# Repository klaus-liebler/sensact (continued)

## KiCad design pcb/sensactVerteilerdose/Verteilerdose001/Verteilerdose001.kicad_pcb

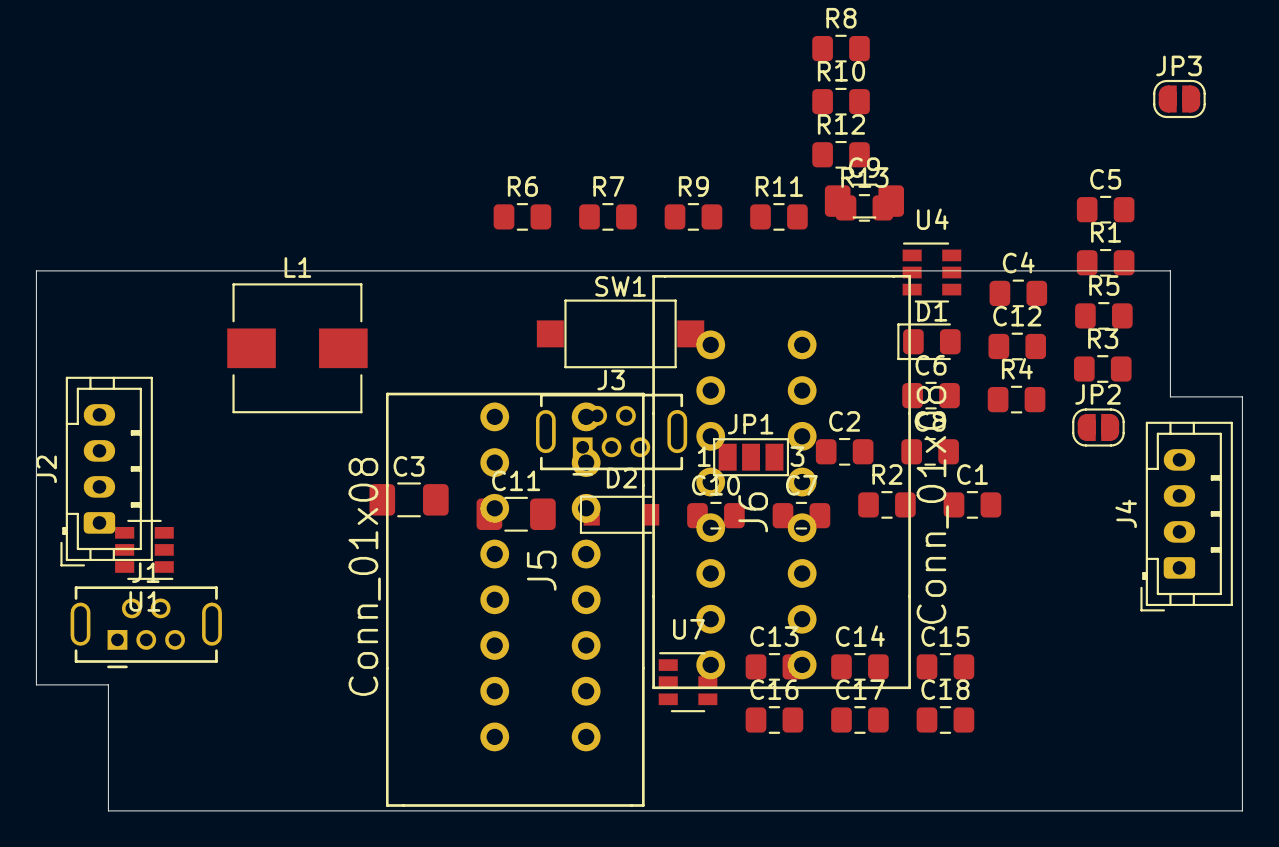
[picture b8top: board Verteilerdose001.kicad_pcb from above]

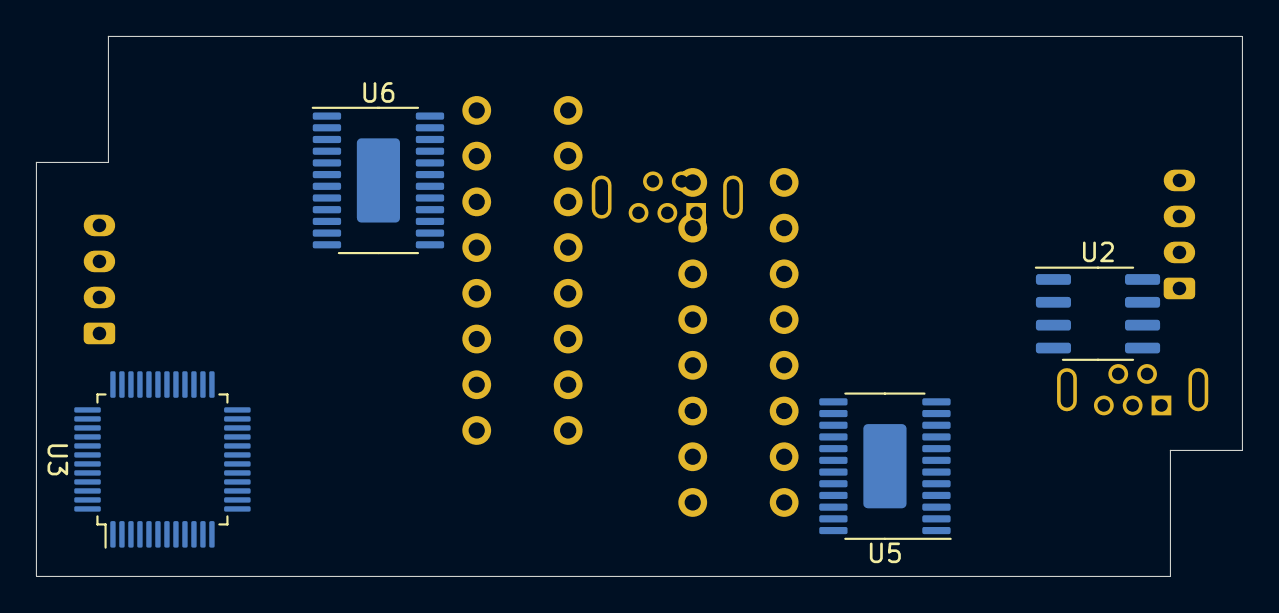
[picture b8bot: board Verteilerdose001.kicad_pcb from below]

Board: 2 copper layers, 67.0 x 30.0 mm, 51 parts (4 on the bottom side), 54 nets, no tracks yet.

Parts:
C1, C2, C4, C5, C6, C7, C8, C10, C12, C13, C14, C15, C16, C17, C18: u1; C_0805_2012Metric_Pad1.15x1.40mm_HandSolder
C3, C9: 4u7; C_1206_3216Metric_Pad1.42x1.75mm_HandSolder
C11: m1; C_1206_3216Metric_Pad1.42x1.75mm_HandSolder
D1: LED; LED_0805_2012Metric_Pad1.15x1.40mm_HandSolder
D2: MBR0540; D_SOD-123
J1: USB; USB_Micro-B_Tensility_54-00023_Vertical
J2: IN; JST_PH_B4B-PH-K_1x04_P2.00mm_Vertical
J3: PROG; USB_Micro-B_Tensility_54-00023_Vertical
J4: OUT; JST_PH_B4B-PH-K_1x04_P2.00mm_Vertical
J5, J6: Conn_01x08; KF141R-8p
JP1: PWRSEL; SolderJumper-3_P1.3mm_Open_Pad1.0x1.5mm_NumberLabels
JP2: JSDA; SolderJumper-2_P1.3mm_Open_RoundedPad1.0x1.5mm
JP3: JSCL; SolderJumper-2_P1.3mm_Open_RoundedPad1.0x1.5mm
L1: 150u; L_Wuerth_HCI-7040
R1: 10k; R_0805_2012Metric_Pad1.15x1.40mm_HandSolder
R2: 100k; R_0805_2012Metric_Pad1.15x1.40mm_HandSolder
R3: R; R_0805_2012Metric_Pad1.15x1.40mm_HandSolder
R4: 3k3; R_0805_2012Metric_Pad1.15x1.40mm_HandSolder
R5, R8, R9, R10, R11: 1k; R_0805_2012Metric_Pad1.15x1.40mm_HandSolder
R6, R7, R12, R13: 10R; R_0805_2012Metric_Pad1.15x1.40mm_HandSolder
SW1: Reset; SW_SPST_CK_RS282G05A3
U1, U7: SRV05-4; SOT-23-6
U2: SN65HVD230; SOIC-8_3.9x4.9mm_P1.27mm
U3: STM32F072C8Tx; LQFP-48_7x7mm_P0.5mm
U4: LMR14206; SOT-23-6
U5, U6: NCV7719; HTSSOP-24-1EP_4.4x7.8mm_P0.65mm_EP3.4x7.8mm_Mask2.4x4.68mm

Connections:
+3V3: C1.1, C3.1, C4.1, C5.1, C6.1, C7.1, C8.1, C11.1, C12.1, C13.1, C14.1, JP1.1, L1.1, R3.1, R4.1, U2.3, U3.1, U3.9, U3.24, U3.36, U3.48, U5.6, U6.6, U7.5
+24V: C9.1, JP1.3, U4.5, U5.16, U5.21, U6.16, U6.21
/IN1: J2.2, J4.2, JP3.1, U1.6, U2.7
/IN2: J2.3, J4.3, JP2.1, U1.4, U2.6
/RX: J3.5, U3.31
/SCL: JP3.2, U3.21
/SDA: JP2.2, U3.22
/SWCLK: J3.1, U3.37
/SWDIO: J3.3, U3.34
/TX: J3.4, U3.30
/USB+: J1.3, U3.33
/USB-: J1.2, U3.32
/VIN: J2.1, J4.1, JP1.2
CANR: U2.4, U3.45
CANT: U2.1, U3.46
CSB: U5.19, U6.19
GND: C1.2, C2.2, C3.2, C4.2, C5.2, C6.2, C7.2, C8.2, C9.2, C11.2, C12.2, C13.2, C14.2, C15.1, C16.1, C17.2, C18.2, D2.2, J1.5, J1.6, J2.4, J3.2, J3.6, J4.4, R1.2, R2.2, R5.2, SW1.2, U2.2, U3.8, U3.23, U3.35, U3.44, U3.47, U4.2, U5.1, U5.12, U5.13, U5.17, U5.18, U5.24, U5.25, U6.1, U6.12, U6.13, U6.17, U6.18, U6.24, U6.25, U7.2
IO0: J5.1, R6.2, U3.18, U5.2
IO1: J5.2, R7.2, U3.19, U5.3
IO2: J5.3, R12.1, U3.14, U5.4
IO3: J5.4, R13.1, U3.39, U5.10
IO4: J5.5, U3.40, U5.11
IO5: J5.6, U3.41, U5.14
IO6: J5.7, U3.42, U5.22
IO7: J5.8, U3.43, U5.23
IO8: J6.1, U3.25, U6.23
IO9: J6.2, U3.26, U6.22
IO10: J6.3, U3.27, U6.14
IO11: J6.4, U3.28, U6.11
IO12: J6.5, U3.10, U6.10
IO13: J6.6, U3.11, U6.4
IO14: J6.7, U3.12, U6.3
IO15: J6.8, U3.13, U6.2
unnamed: C2.1, SW1.1, U3.7
unnamed: C10.1, D2.1, L1.2, U4.6
unnamed: C10.2, U4.1
unnamed: C15.2, R8.2
unnamed: C16.2, R9.1
unnamed: C17.1, R10.2
unnamed: C18.1, R11.1
unnamed: D1.1, U3.20
unnamed: D1.2, R3.2
unnamed: J1.4, R2.1
unnamed: R1.1, U2.8
unnamed: R4.2, R5.1, U4.3
unnamed: R6.1, R8.1, U7.1
unnamed: R7.1, R9.2, U7.3
unnamed: R10.1, R12.2, U7.4
unnamed: R11.2, R13.2, U7.6
OUT_EN: U5.8, U6.8
SOSI: U5.7, U6.5
SPI_CLK: U3.15, U6.20
SPI_MISO: U3.16, U6.7
SPI_MOSI: U3.17, U5.5
